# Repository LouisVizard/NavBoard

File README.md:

<div align="center">

# 🛰️ Navigation Board PCB

**A compact, 6-layer embedded navigation platform for real-time sensor fusion and wireless telemetry**

</div>

---

## 📌 Overview

The **Navigation Board** is a custom PCB designed as a dedicated navigation and state estimation platform. It integrates GNSS positioning, inertial sensing, and wireless communication onto a single, compact board — enabling real-time vehicle attitude estimation via a Kalman filter and live data streaming to a host computer for visualization.

> The hardware is complete and functional. Active development is now focused on firmware (EKF implementation) and the host-side Python visualization pipeline.

---

## 🖼️ Board Preview

| Isometric Top | Isometric Bottom |
|:---:|:---:|
|  |  |

<details>
<summary>📐 PCB Layout</summary>
<br>

</details>

<details>
<summary>🔌 Full Schematic</summary>
<br>

</details>

---

## ⚡ Specifications

| Parameter | Value |
|-----------|-------|
| **MCU** | STM32F4CEU6 |
| **GNSS Receiver** | u-blox NEO-M9N |
| **IMU** | 9DOF — Accelerometer + Gyroscope + Magnetometer |
| **Wireless** | nRF24L01 (2.4 GHz RF) |
| **Power Input** | Single-cell LiPo + USB-C charging |
| **PCB Stackup** | 6-layer, impedance controlled |

---

## 🏗️ System Architecture

```
┌─────────────┐     ┌─────────────────────────┐     ┌──────────────────┐     ┌──────────────────┐
│  GNSS       │     │                         │     │                  │     │                  │
│  NEO-M9N    │────▶│     STM32F4CEU6         │────▶│  nRF24L01        │────▶│  Host PC         │
│  (UART)     │     │   Kalman Filter /        │     │  2.4 GHz RF Link │     │  Python Viz      │
├─────────────┤     │   Sensor Fusion          │     │                  │     │                  │
│  IMU 9DOF   │     │                         │     │                  │     │                  │
│  (SPI/I2C)  │────▶│                         │     │                  │     │                  │
└─────────────┘     └─────────────────────────┘     └──────────────────┘     └──────────────────┘
```

**Goal:** Fuse absolute positioning (GNSS) with high-rate inertial data (IMU) using an Extended Kalman Filter to estimate real-time orientation and motion, then stream state estimates wirelessly to a host computer for visualization.

---

## 🔧 Design Details

### Hardware Integration

The board centers around the **STM32F4** MCU, which interfaces with:
- **NEO-M9N** GNSS receiver over **UART** for global positioning
- **9DOF IMU** over **SPI/I2C** for high-rate motion sensing
- **nRF24L01** providing a low-latency **2.4 GHz RF link** to stream processed state estimates to an external computer

### Power System

Powered by a single-cell **LiPo battery** with onboard **USB-C charging** circuitry. Independent regulation stages supply stable rails for:
- RF front-end
- Digital logic
- Analog sensing paths

This architecture minimizes noise coupling into sensitive IMU measurements.

### PCB Stackup

A **6-layer stackup** was chosen to provide:
- Controlled impedance for RF and GNSS antenna traces
- Solid ground referencing across all layers
- Clean power distribution

Dedicated power and ground planes minimize EMI and improve signal integrity throughout.

---

## 📊 PCB Stackup Details

The full layer stackup with impedance targets and material specifications is documented in the design spreadsheet:

📄 **[View Stackup Spreadsheet (Google Sheets)](https://docs.google.com/spreadsheets/d/1y8UFBo5hvFj5DNxBOYgQXF0sVpvpMorS/preview)**

---

## 🗺️ Roadmap

The hardware platform is complete. Next steps are focused on firmware and software:

- [ ] Implement **Extended Kalman Filter (EKF)** for GNSS + IMU fusion on STM32F4
- [ ] Tune process and measurement noise covariance matrices
- [ ] Stream state estimates over nRF24L01 RF link
- [ ] Develop **Python visualization** for real-time attitude display
- [ ] Validate filter output against ground truth measurements

---

## 🛠️ Tech Stack

| Layer | Technology |
|-------|-----------|
| **Hardware Design** | KiCad |
| **Firmware** | C (STM32 HAL / bare-metal) |
| **Host Software** | Python |
| **Comms Protocol** | nRF24L01 2.4 GHz |

---

## 👤 Author

**Luis Martinez**

---

<div align="center">
<sub>Built with KiCad · STM32 · u-blox · nRF24L01</sub>
</div>

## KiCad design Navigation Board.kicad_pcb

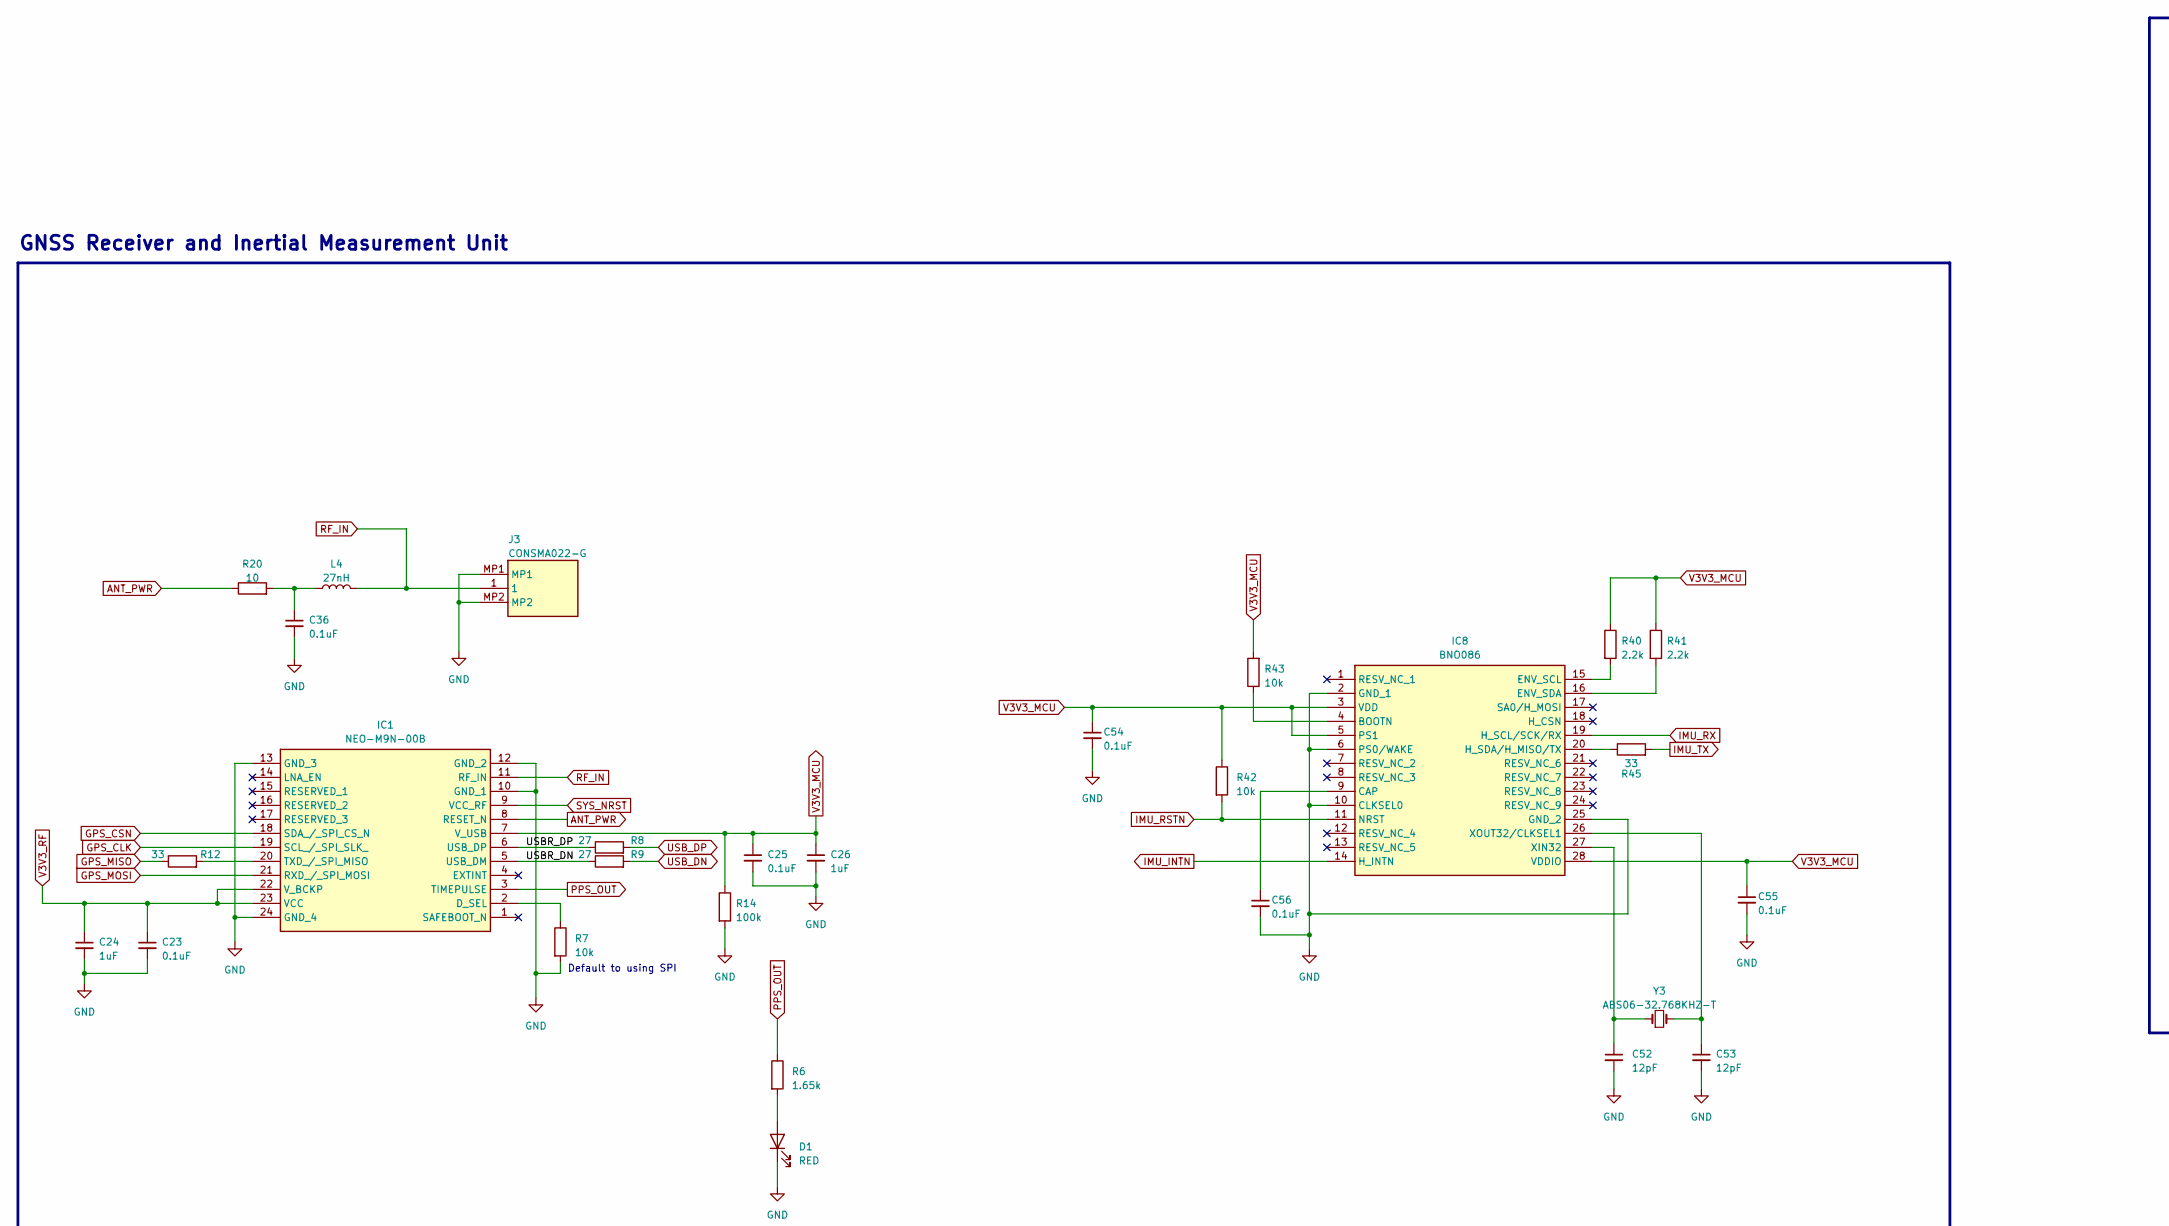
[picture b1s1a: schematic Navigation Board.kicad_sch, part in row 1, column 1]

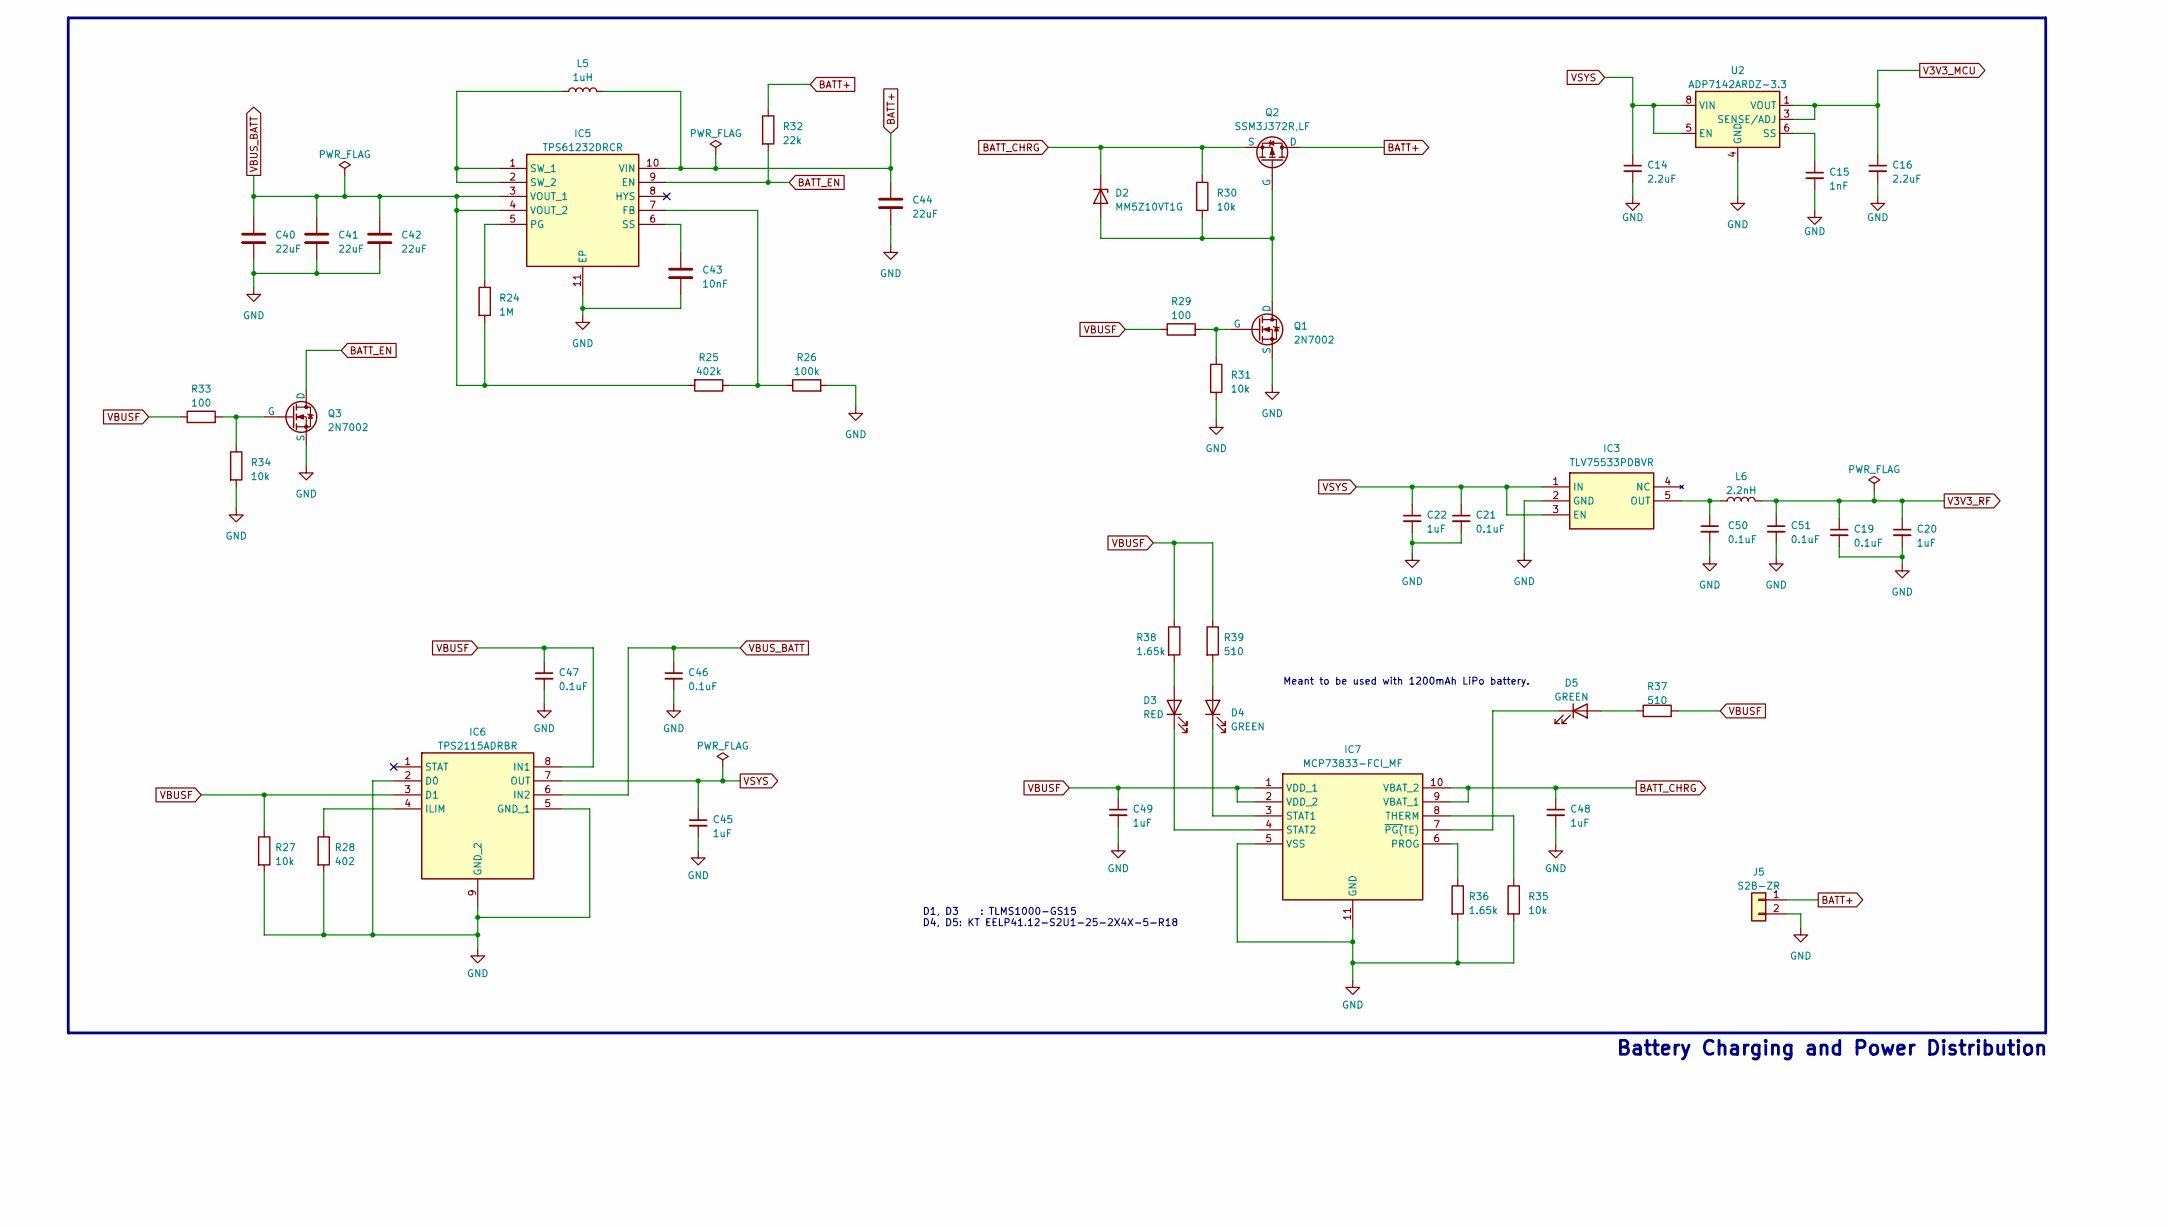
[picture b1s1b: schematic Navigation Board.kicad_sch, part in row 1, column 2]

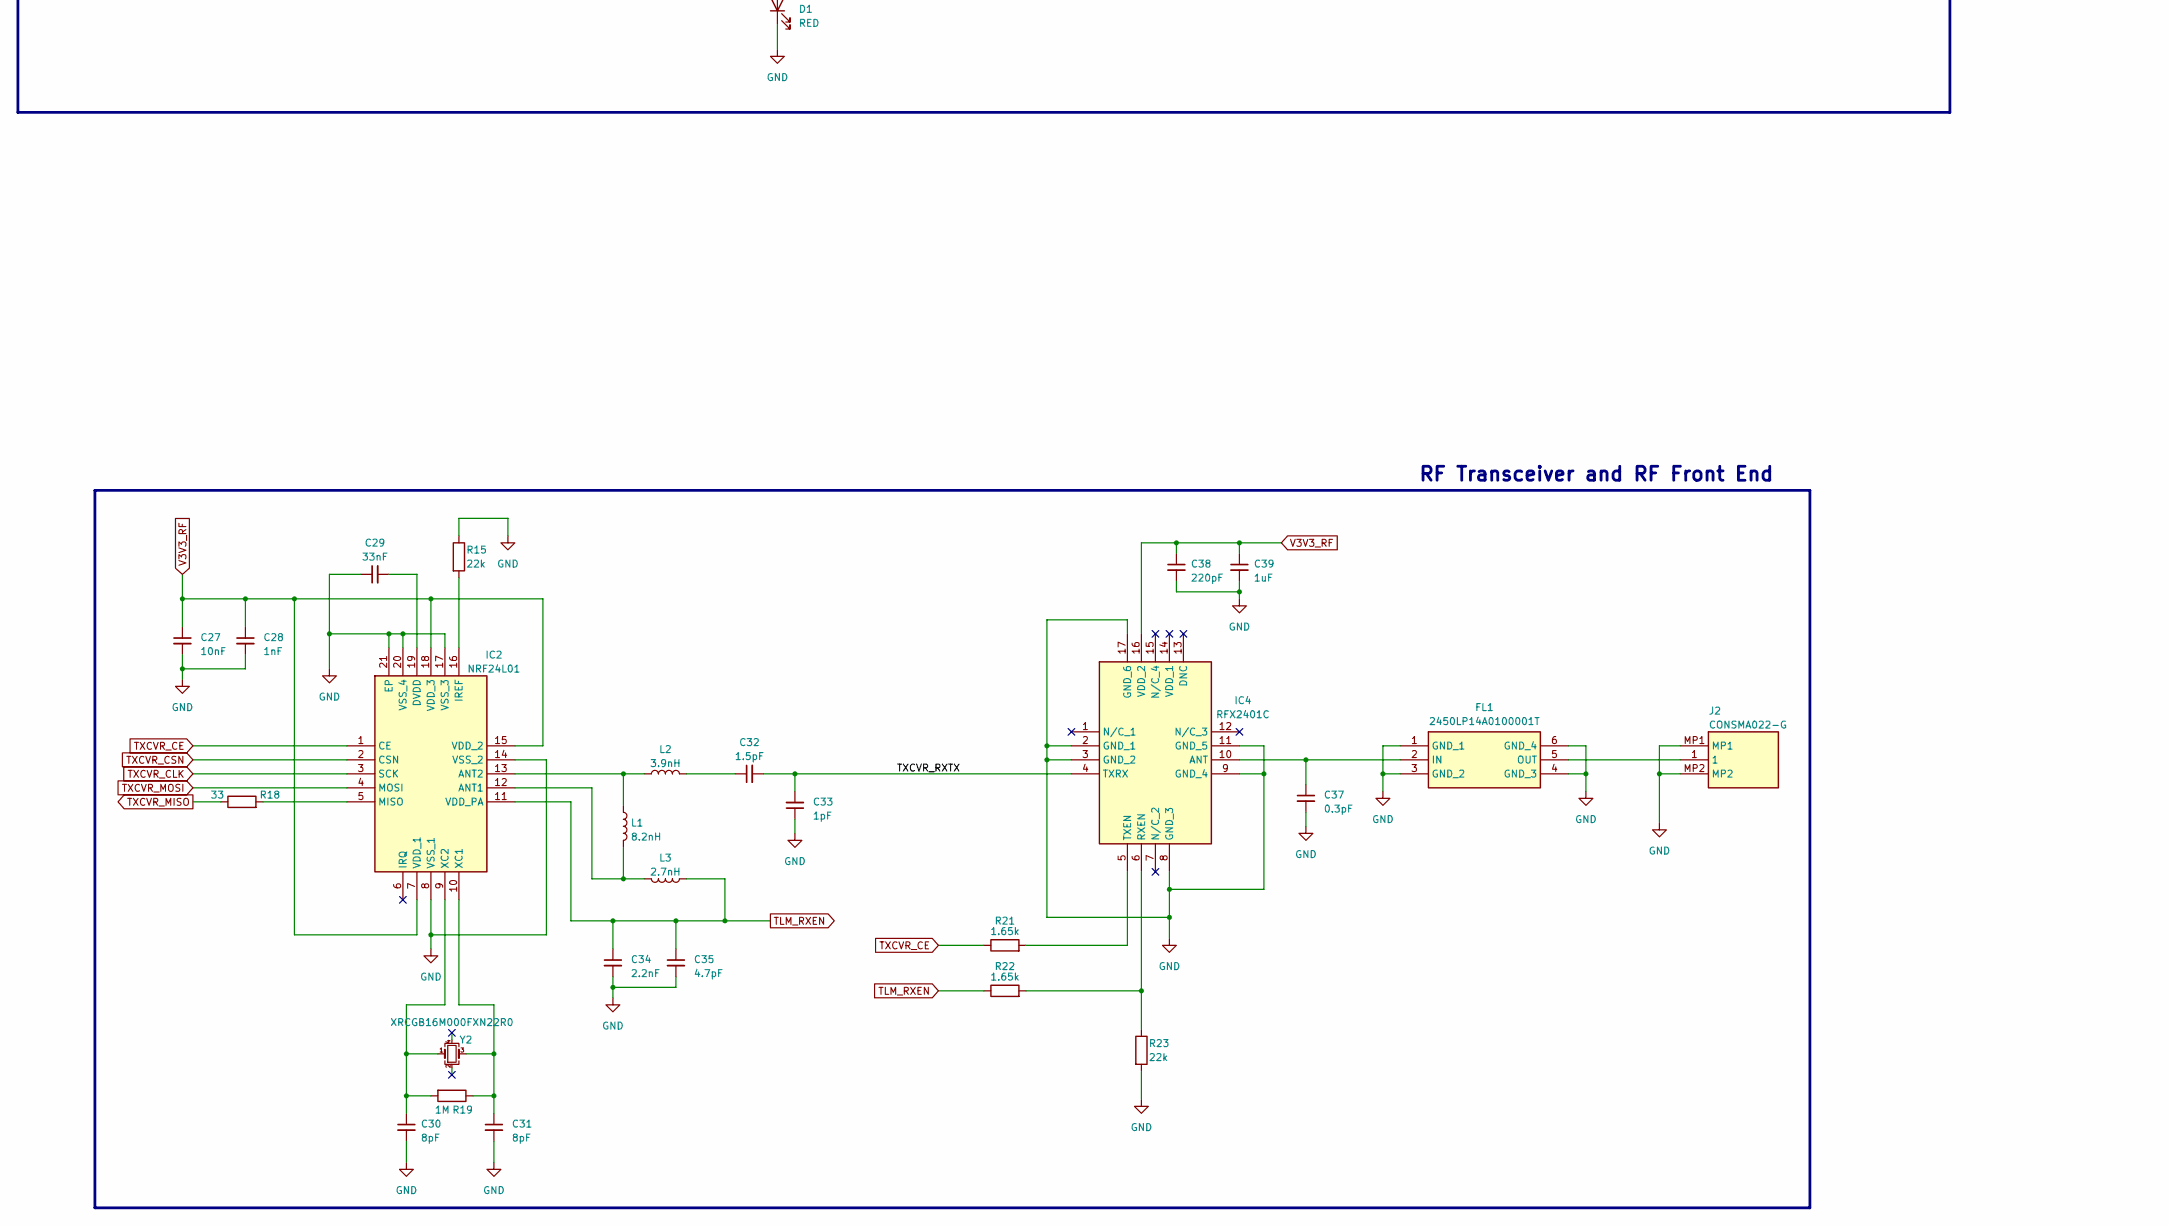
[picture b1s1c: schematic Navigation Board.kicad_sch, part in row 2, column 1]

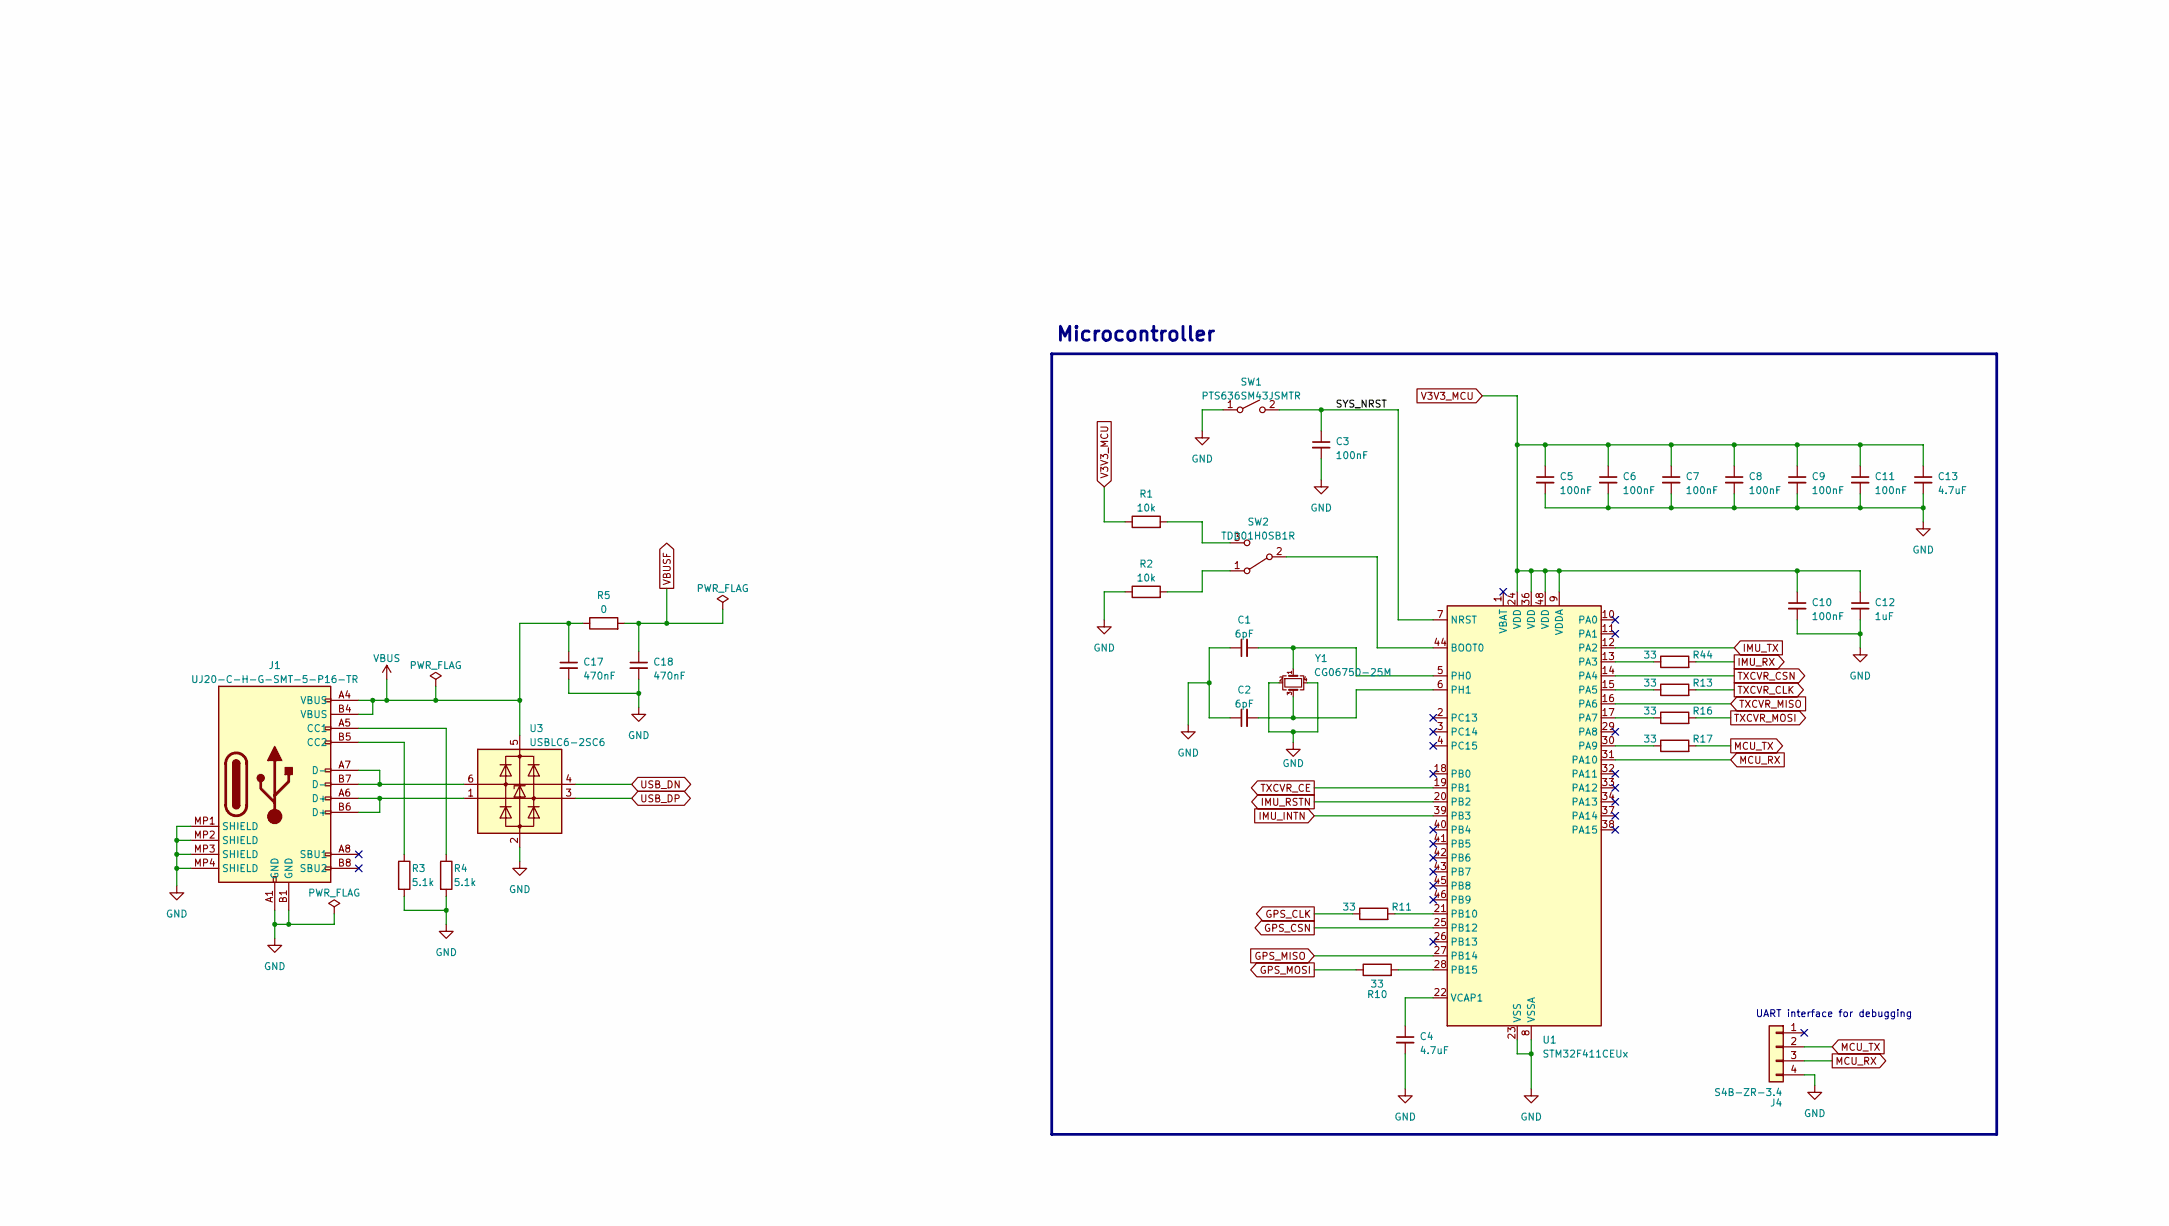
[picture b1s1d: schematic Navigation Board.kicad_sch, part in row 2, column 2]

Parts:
C1, C2: 6pF; C_0603_1608Metric
C3, C5, C6, C7, C8, C9, C10, C11: 100nF; C_0603_1608Metric
C4, C13: 4.7uF; C_0805_2012Metric
C12, C20, C22, C24, C26, C39, C45, C48, C49: 1uF; C_0603_1608Metric
C14, C16: 2.2uF; C_0603_1608Metric
C15, C28: 1nF; C_0603_1608Metric
C17, C18: 470nF; C_0603_1608Metric
C19, C21, C23, C25, C36, C46, C47, C50, C51: 0.1uF; C_0603_1608Metric
C27: 10nF; C_0603_1608Metric
C29: 33nF; C_0402_1005Metric
C30, C31: 8pF; C_0402_1005Metric
C32: 1.5pF; C_0402_1005Metric
C33: 1pF; C_0402_1005Metric
C34: 2.2nF; C_0402_1005Metric
C35: 4.7pF; C_0402_1005Metric
C37: 0.3pF; C_0402_1005Metric
C38: 220pF; C_0603_1608Metric
C40, C41, C42, C44: 22uF; C_1206_3216Metric
C43: 10nF; C_0805_2012Metric
C52, C53: 12pF; C_0402_1005Metric
C54, C55, C56: 0.1uF; C_0402_1005Metric
D1, D3: RED; D_0603_1608Metric
D2: MM5Z10VT1G
D4, D5: GREEN; D_0603_1608Metric
FL1: 2450LP14A0100001T; Manufacturer_Part_Number 2450LP14A0100001T
IC1: NEO-M9N-00B; NEOM9N00B; Mouser Part Number 377-NEO-M9N-00B
IC2: NRF24L01; nRF24L01; Mouser Part Number 949-NRF24L01
IC3: TLV75533PDBVR; Mouser Part Number 595-TLV75533PDBVR
IC4: RFX2401C; Mouser Part Number 477-RFX2401C
IC5: TPS61232DRCR; Mouser Part Number 595-TPS61232DRCR
IC6: TPS2115ADRBR; Mouser Part Number 595-TPS2115ADRBR
IC7: MCP73833-FCI_MF; Mouser Part Number 579-MCP73833-FCI/MF
IC8: BNO086; Mouser Part Number 526-BNO086
J1: UJ20-C-H-G-SMT-5-P16-TR
J2, J3: CONSMA022-G; CONSMA022G; Mouser Part Number 712-CONSMA022-G
J4: S4B-ZR-3.4; S4BZR34LFSN
J5: S2B-ZR
L1: 8.2nH; L_0603_1608Metric
L2: 3.9nH; L_0603_1608Metric
L3: 2.7nH; L_0603_1608Metric
L4: 27nH; L_0603_1608Metric
L5: 1uH; L_Vishay_IHLP-1616
L6: 2.2nH; L_0402_1005Metric
Q1, Q3: 2N7002
Q2: SSM3J372R,LF; SSM3J372RLF
R1, R2, R7, R27, R30, R31, R34, R35, R42, R43: 10k; R_0603_1608Metric
R3, R4: 5.1k; R_0603_1608Metric
R5: 0; R_1210_3225Metric
R6, R21, R22, R36, R38: 1.65k; R_0603_1608Metric
R8, R9: 27; R_0603_1608Metric
R10, R11, R12, R13, R16, R17, R18, R44, R45: 33; R_0603_1608Metric
R14, R26: 100k; R_0805_2012Metric
R15, R23, R32: 22k; R_0805_2012Metric
R19, R24: 1M; R_0603_1608Metric
R20: 10; R_0805_2012Metric
R25: 402k; R_0603_1608Metric
R28: 402; R_0402_1005Metric
R29, R33: 100; R_0603_1608Metric
R37, R39: 510; R_0603_1608Metric
R40, R41: 2.2k; R_0603_1608Metric
SW1: PTS636SM43JSMTR; PTS636SM43JSMTRLFS
SW2: TDD01H0SB1R
U1: STM32F411CEUx; STM32F411CEU6
U2: ADP7142ARDZ-3.3
U3: USBLC6-2SC6; SOT-23-6
Y1: CG06750-25M
Y2: XRCGB16M000FXN22R0
Y3: ABS06-32.768KHZ-T

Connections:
/TXCVR_RXTX: C32.2, C33.2, IC4.4 (TXRX)
/USBR_DN: IC1.5 (USB_DM), R9.1
/USBR_DP: IC1.6 (USB_DP), R8.1
ANT_PWR: IC1.8 (RESET_N), R20.1
BATT+: C44.1, IC5.10 (VIN), J5.1, L5.2, Q2.1 (D), R32.1
BATT_CHRG: C48.1, D2.1 (K), IC7.9 (VBAT_1), IC7.10 (VBAT_2), Q2.3 (S), R30.1
BATT_EN: IC5.9 (EN), Q3.1 (D), R32.2
GND: C1.1, C2.1, C3.2, C4.2, C5.2, C6.2, C7.2, C8.2, C9.2, C10.2, C11.2, C12.2, C13.2, C14.2, C15.2, C16.2, C17.2, C18.2, C19.2, C20.2, C21.2, C22.2, C23.2, C24.2, C25.2, C26.2, C27.2, C28.2, C29.1, C30.2, C31.2, C33.1, C34.2, C35.2, C36.2, C37.2, C38.2, C39.2, C40.2, C41.2, C42.2, C43.2, C44.2, C45.2, C46.2, C47.2, C48.2, C49.2, C50.2, C51.2, C52.2, C53.2, C54.2, C55.2, C56.2, D1.1 (K), FL1.1 (GND_1), FL1.3 (GND_2), FL1.4 (GND_3), FL1.6 (GND_4), IC1.10 (GND_1), IC1.12 (GND_2), IC1.13 (GND_3), IC1.24 (GND_4), IC2.8 (VSS_1), IC2.14 (VSS_2), IC2.17 (VSS_3), IC2.20 (VSS_4), IC2.21 (EP), IC3.2 (GND), IC4.2 (GND_1), IC4.3 (GND_2), IC4.8 (GND_3), IC4.9 (GND_4), IC4.11 (GND_5), IC4.17 (GND_6), IC5.11 (EP), IC6.2 (D0), IC6.5 (GND_1), IC6.9 (GND_2), IC7.5 (VSS), IC7.11 (GND), IC8.2 (GND_1), IC8.6 (PS0/WAKE), IC8.10 (CLKSEL0), IC8.25 (GND_2), J1.A1 (GND), J1.B1 (GND), J1.MP1 (SHIELD), J1.MP2 (SHIELD), J1.MP3 (SHIELD), J1.MP4 (SHIELD), J2.MP1, J2.MP2, J3.MP1, J3.MP2, J4.4, J5.2, Q1.3 (S), Q3.3 (S), R2.1, R3.2, R4.2, R7.2, R14.2, R15.1, R23.2, R26.2, R27.2, R28.2, R31.2, R34.2, R35.2, R36.2, SW1.1 (A), U1.8 (VSSA), U1.23 (VSS), U1.35 (VSS), U1.47 (VSS), U1.49 (VSS), U2.4 (GND), U2.9 (GND), U3.2 (GND), Y1.2, Y1.4
GPS_CLK: IC1.19 (SCL_/_SPI_SLK_), R11.1
GPS_CSN: IC1.18 (SDA_/_SPI_CS_N), U1.25 (PB12)
GPS_MISO: R12.1, U1.27 (PB14)
GPS_MOSI: IC1.21 (RXD_/_SPI_MOSI), R10.1
IMU_INTN: IC8.14 (H_INTN), U1.39 (PB3)
IMU_RSTN: IC8.11 (NRST), R42.2, U1.20 (PB2)
IMU_RX: IC8.19 (H_SCL/SCK/RX), R44.2
IMU_TX: R45.2, U1.12 (PA2)
MCU_RX: J4.3, U1.31 (PA10)
MCU_TX: J4.2, R17.2
unnamed: C32.1, L2.2
unnamed: C36.1, L4.1, R20.2
unnamed: D1.2 (A), R6.2
unnamed: D2.2 (A), Q1.1 (D), Q2.2 (G), R30.2
unnamed: D3.2 (A), R38.2
unnamed: D3.1 (K), IC7.4 (STAT2)
unnamed: D4.2 (A), R39.2
unnamed: D4.1 (K), IC7.3 (STAT1)
unnamed: D5.2 (A), R37.1
unnamed: D5.1 (K), IC7.7 (~PG(TE))
unnamed: C37.1, FL1.2 (IN), IC4.10 (ANT)
unnamed: FL1.5 (OUT), J2.1
unnamed: IC1.2 (D_SEL), R7.1
unnamed: IC1.20 (TXD_/_SPI_MISO), R12.2
unnamed: IC2.12 (ANT1), L1.2, L3.2
unnamed: IC2.13 (ANT2), L1.1, L2.1
unnamed: C29.2, IC2.19 (DVDD)
unnamed: IC2.16 (IREF), R15.2
unnamed: IC2.5 (MISO), R18.2
unnamed: C31.1, IC2.10 (XC1), R19.1, Y2.3
unnamed: C30.1, IC2.9 (XC2), R19.2, Y2.1
unnamed: C50.1, IC3.5 (OUT), L6.1
unnamed: IC4.6 (RXEN), R22.2, R23.1
unnamed: IC4.5 (TXEN), R21.2
unnamed: IC5.7 (FB), R25.1, R26.1
unnamed: IC5.5 (PG), R24.1
unnamed: C43.1, IC5.6 (SS)
unnamed: IC5.1 (SW_1), IC5.2 (SW_2), L5.1
unnamed: IC6.4 (ILIM), R28.1
unnamed: IC7.6 (PROG), R36.1
unnamed: IC7.8 (THERM), R35.1
unnamed: IC8.4 (BOOTN), R43.1
unnamed: C56.1, IC8.9 (CAP)
unnamed: IC8.15 (ENV_SCL), R40.2
unnamed: IC8.16 (ENV_SDA), R41.2
unnamed: IC8.20 (H_SDA/H_MISO/TX), R45.1
unnamed: C52.1, IC8.27 (XIN32), Y3.1
unnamed: C53.1, IC8.26 (XOUT32/CLKSEL1), Y3.2
unnamed: J1.A5 (CC1), R4.1
unnamed: J1.B5 (CC2), R3.1
unnamed: J1.A6 (D+), J1.B6 (D+), U3.1 (I/O1)
unnamed: J1.A7 (D-), J1.B7 (D-), U3.6 (I/O1)
unnamed: Q1.2 (G), R29.2, R31.1
unnamed: Q3.2 (G), R33.2, R34.1
unnamed: R2.2, SW2.1 (A)
unnamed: SW2.2 (B), U1.44 (BOOT0)
unnamed: R1.2, SW2.3 (C)
unnamed: R44.1, U1.13 (PA3)
unnamed: R13.1, U1.15 (PA5)
unnamed: R16.1, U1.17 (PA7)
unnamed: R17.1, U1.30 (PA9)
unnamed: R11.2, U1.21 (PB10)
unnamed: R10.2, U1.28 (PB15)
unnamed: C1.2, U1.5 (PH0), Y1.1
unnamed: C2.2, U1.6 (PH1), Y1.3
unnamed: C4.1, U1.22 (VCAP1)
unnamed: C15.1, U2.6 (SS)
PPS_OUT: IC1.3 (TIMEPULSE), R6.1
RF_IN: IC1.11 (RF_IN), J3.1, L4.2
SYS_NRST: C3.1, IC1.9 (VCC_RF), SW1.2 (B), U1.7 (NRST)
TLM_RXEN: C34.1, C35.1, IC2.11 (VDD_PA), L3.1, R22.1
TXCVR_CE: IC2.1 (CE), R21.1, U1.19 (PB1)
TXCVR_CLK: IC2.3 (SCK), R13.2
TXCVR_CSN: IC2.2 (CSN), U1.14 (PA4)
TXCVR_MISO: R18.1, U1.16 (PA6)
TXCVR_MOSI: IC2.4 (MOSI), R16.2
USB_DN: R9.2, U3.4 (I/O2)
USB_DP: R8.2, U3.3 (I/O2)
V3V3_MCU: C5.1, C6.1, C7.1, C8.1, C9.1, C10.1, C11.1, C12.1, C13.1, C16.1, C25.1, C26.1, C54.1, C55.1, IC1.7 (V_USB), IC8.3 (VDD), IC8.5 (PS1), IC8.28 (VDDIO), R1.1, R14.1, R40.1, R41.1, R42.1, R43.2, U1.9 (VDDA), U1.24 (VDD), U1.36 (VDD), U1.48 (VDD), U2.1 (VOUT), U2.2 (VOUT), U2.3 (SENSE/ADJ)
V3V3_RF: C19.1, C20.1, C23.1, C24.1, C27.1, C28.1, C38.1, C39.1, C51.1, IC1.22 (V_BCKP), IC1.23 (VCC), IC2.7 (VDD_1), IC2.15 (VDD_2), IC2.18 (VDD_3), IC4.16 (VDD_2), L6.2
VBUS: C17.1, J1.A4 (VBUS), J1.B4 (VBUS), R5.1, U3.5 (VBUS)
VBUSF: C18.1, C47.1, C49.1, IC6.3 (D1), IC6.8 (IN1), IC7.1 (VDD_1), IC7.2 (VDD_2), R5.2, R27.1, R29.1, R33.1, R37.2, R38.1, R39.1
VBUS_BATT: C40.1, C41.1, C42.1, C46.1, IC5.3 (VOUT_1), IC5.4 (VOUT_2), IC6.6 (IN2), R24.2, R25.2
VSYS: C14.1, C21.1, C22.1, C45.1, IC3.1 (IN), IC3.3 (EN), IC6.7 (OUT), U2.5 (EN), U2.7 (VIN), U2.8 (VIN)

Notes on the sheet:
D1, D3 : TLMS1000-GS15 D4, D5: KT EELP41.12-S2U1-25-2X4X-5-R18
UART interface for debugging
Default to using SPI
Microcontroller
Battery Charging and Power Distribution
Meant to be used with 1200mAh LiPo battery.
GNSS Receiver and Inertial Measurement Unit
RF Transceiver and RF Front End

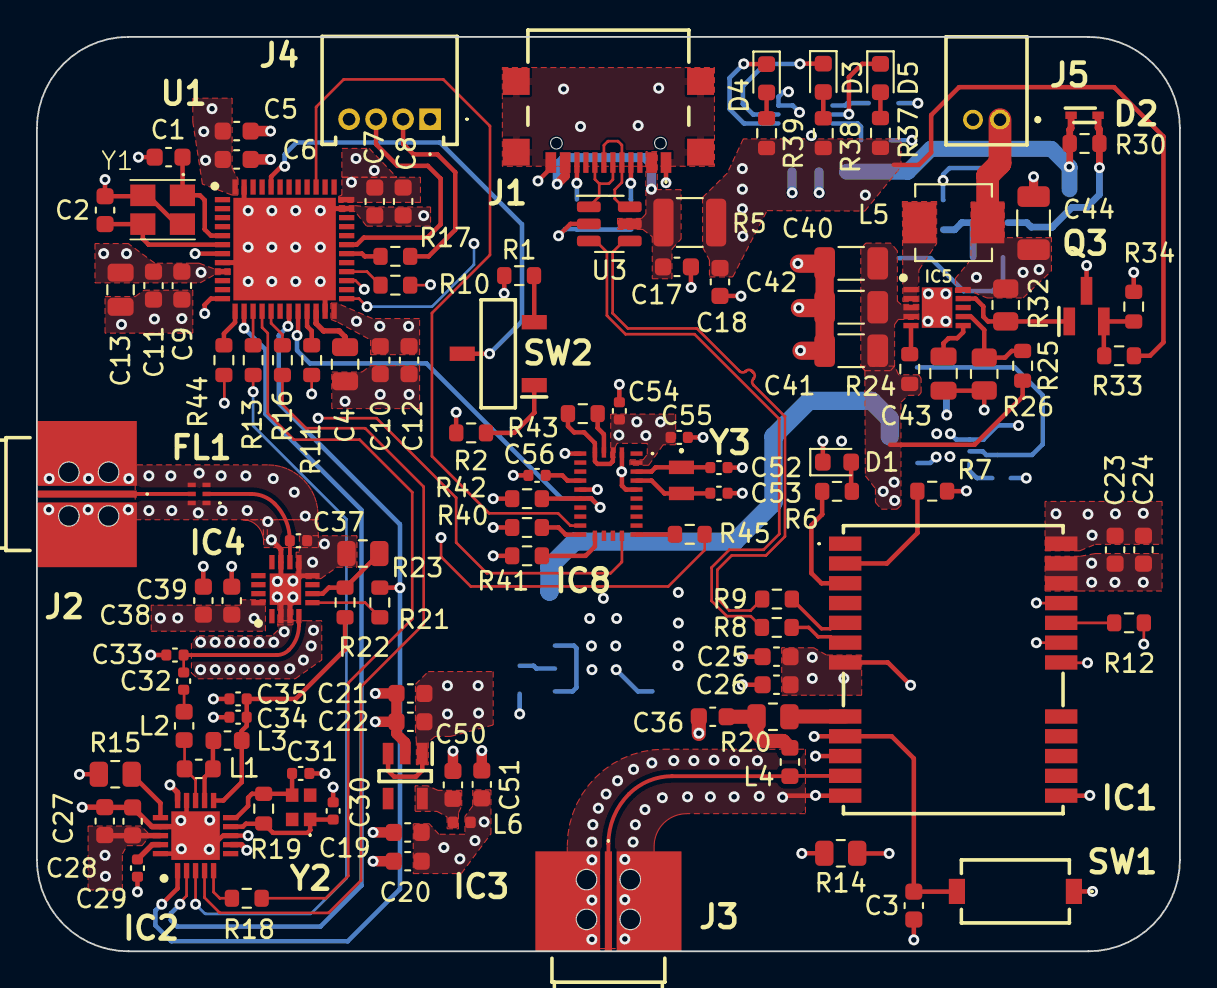
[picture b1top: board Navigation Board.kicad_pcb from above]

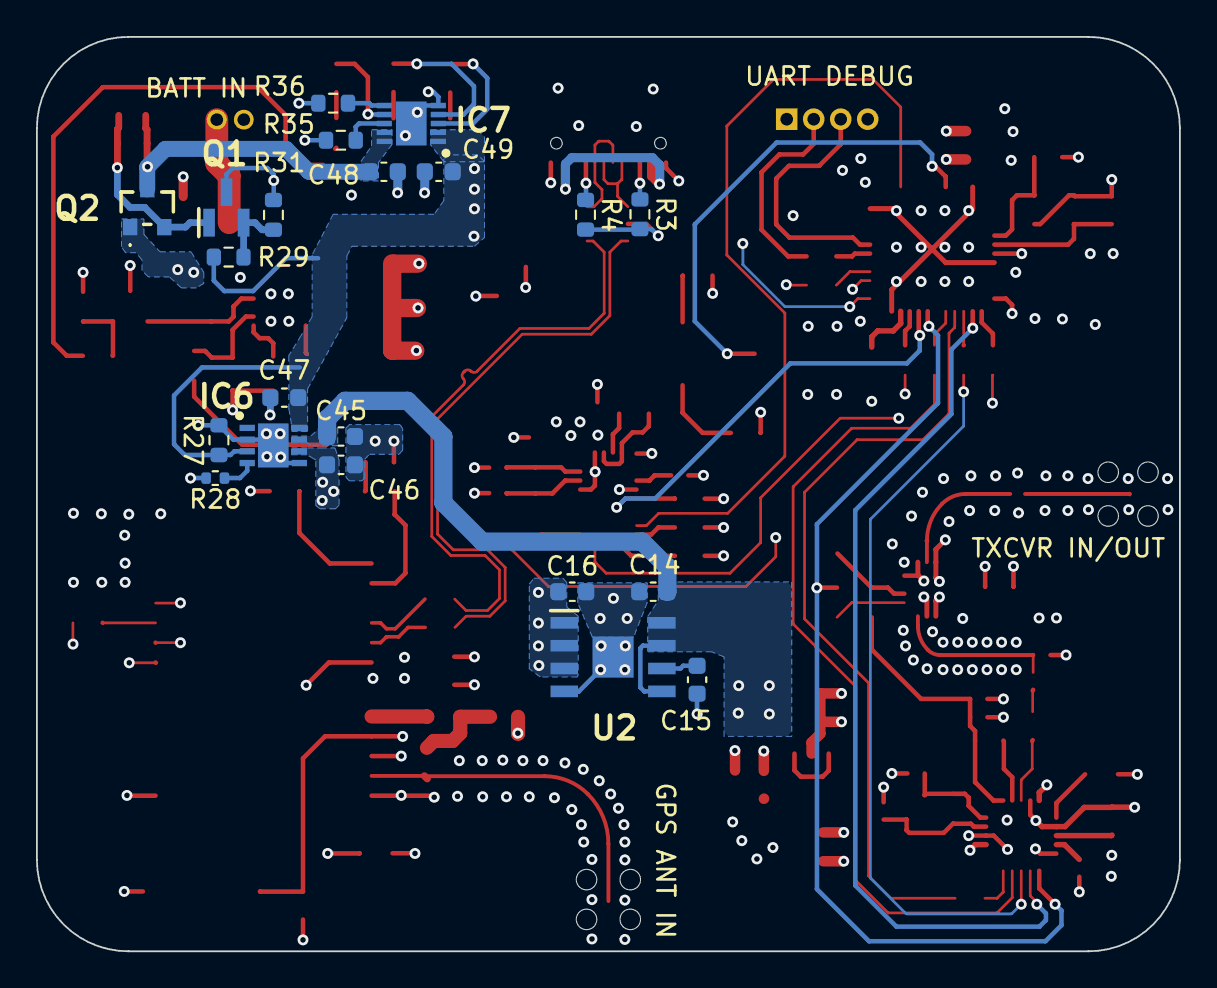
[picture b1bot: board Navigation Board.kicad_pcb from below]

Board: 6 copper layers, 63.5 x 50.8 mm, 137 parts (21 on the bottom side), 92 nets.

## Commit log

2026-06-06 Removed .DS_Store file
2026-06-06 Removed .DS_Store file from 3D_Models file
2026-06-06 Added readme
2026-06-07 Moved pi filter to input of LDO from output. Also added drill table
